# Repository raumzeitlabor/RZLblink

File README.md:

RZLblink
========

RZLblink is a do-it-yourself clone of the blink(1) by ThingM. (https://github.com/todbot/blink1/)
This work is licensed under a Creative Commons Attribution Share Alike 3.0 License.

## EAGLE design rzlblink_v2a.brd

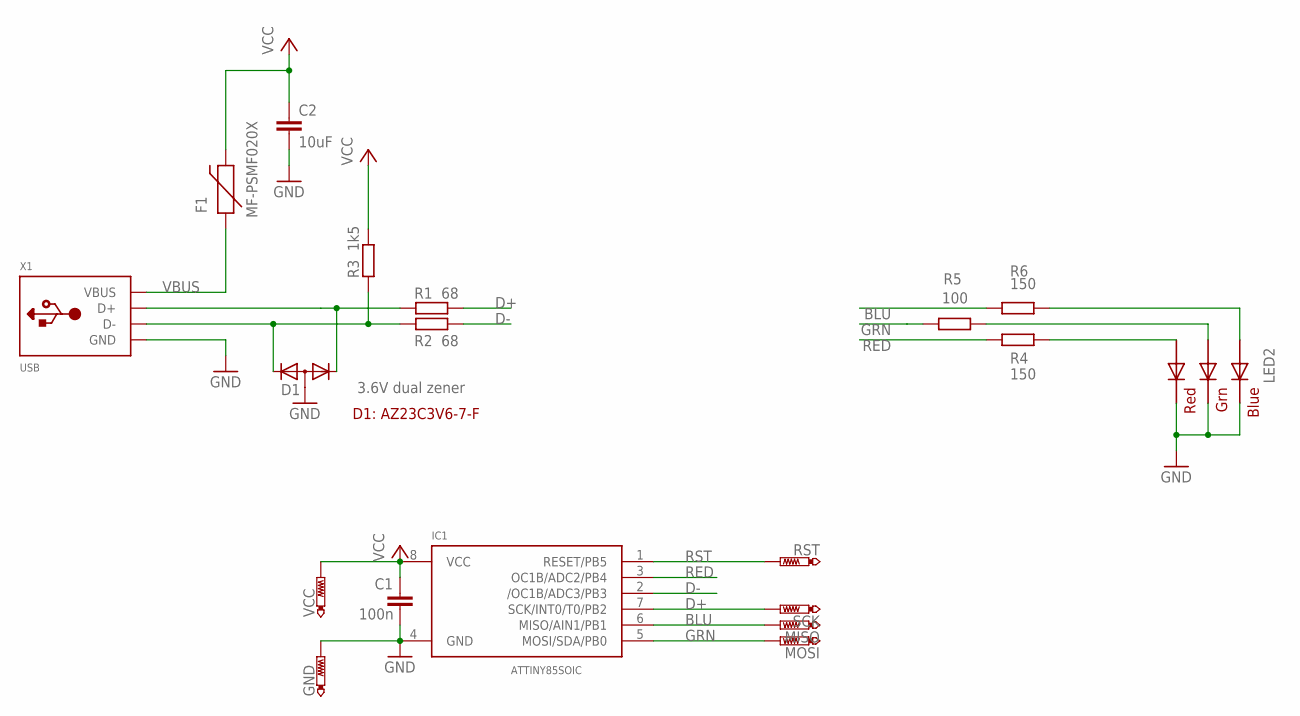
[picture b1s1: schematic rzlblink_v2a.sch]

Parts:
C1: 100n; C0805
C2: 10uF; C0805
D1: 3.6V dual zener; SOT23
F1: MF-PSMF020X; 0805
GND: PTR1TP10R; TP10R
IC1: ATTINY85SOIC; SO08-EIAJ
LED2: RGBLED5050
MISO: PTR1TP10R; TP10R
MOSI: PTR1TP10R; TP10R
R1, R2: 68; R1206
R3: 1k5; R0805
R4, R6: 150; R0805
R5: 100; R0805
RST: PTR1TP10R; TP10R
SCK: PTR1TP10R; TP10R
VCC: PTR1TP10R; TP10R
X1: USB; MOLEX-48037-1000

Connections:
BLU: IC1.6 (MISO/AIN1/PB1), MISO.TP, R6.1
D+: IC1.7 (SCK/INT0/T0/PB2), R1.1, SCK.TP
D-: IC1.2 (/OC1B/ADC3/PB3), R2.1
GND: C1.2, C2.2, D1.3 (A), GND.TP, IC1.4 (GND), LED2.4 (BLUE_C), LED2.5 (RED_C), LED2.6 (GREEN_C), X1.4 (GND)
GRN: IC1.5 (MOSI/SDA/PB0), MOSI.TP, R5.1
unnamed: D1.1 (K1), R1.2, X1.3 (D+)
unnamed: D1.2 (K2), R2.2, R3.2, X1.2 (D-)
RBLU: LED2.3 (BLUE_A), R6.2
RED: IC1.3 (OC1B/ADC2/PB4), R4.1
RGRN: LED2.1 (GREEN_A), R5.2
RRED: LED2.2 (RED_A), R4.2
RST: IC1.1 (RESET/PB5), RST.TP
VBUS: F1.1, X1.1 (VBUS)
VCC: C1.1, C2.1, F1.2, IC1.8 (VCC), R3.1, VCC.TP

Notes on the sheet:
D1: AZ23C3V6-7-F

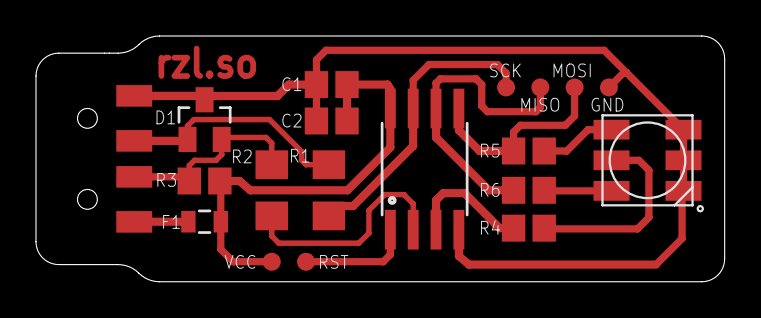
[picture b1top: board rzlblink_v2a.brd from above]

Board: 2 copper layers, 38.3 x 13.7 mm, 19 parts (0 on the bottom side), 14 nets.

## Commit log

2013-05-15 add schematics, update readme

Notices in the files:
rzlblink_v2a.brd:
under Creative Commons Attribution
